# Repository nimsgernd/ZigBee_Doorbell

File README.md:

# ZigBee_Doorbell
I wanted to try to make a nice simple ZigBee doorbell system using some cheap STM32WBA chips and some small Li-Po batteries.

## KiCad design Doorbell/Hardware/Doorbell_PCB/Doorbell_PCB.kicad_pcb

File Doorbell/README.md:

# Doorbell

This folder contains all the files for the doorbell side of the project.

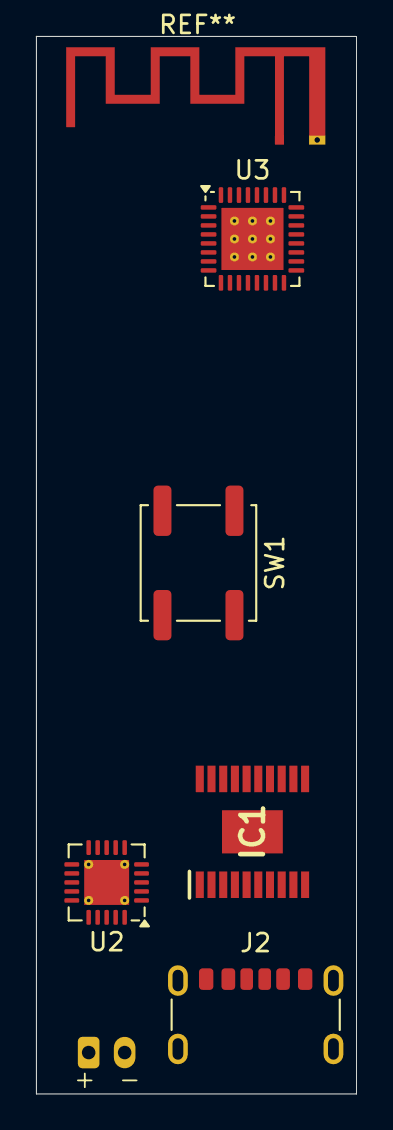
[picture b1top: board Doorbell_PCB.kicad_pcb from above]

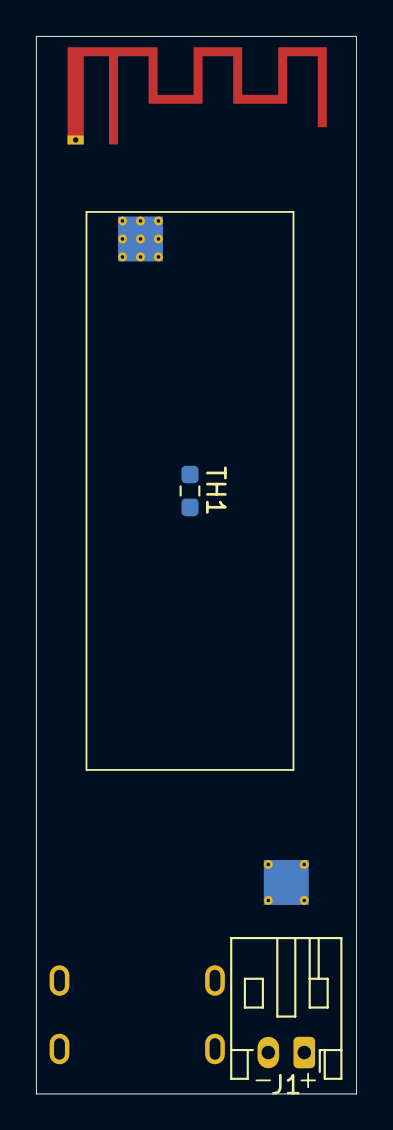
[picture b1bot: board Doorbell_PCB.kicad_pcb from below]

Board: 2 copper layers, 17.8 x 58.8 mm, 7 parts (2 on the bottom side), 5 nets, no tracks yet.

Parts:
IC1: TPS75301QPWP; SOP65P640X120-21N
J1: Conn_01x02_Socket; JST_PH_S2B-PH-K_1x02_P2.00mm_Horizontal
J2: USB_C_Receptacle_PowerOnly_6P; USB_C_Receptacle_GCT_USB4125-xx-x_6P_TopMnt_Horizontal
SW1: SW_Push; SW_Push_1P1T_NO_CK_KSC9xxJ
TH1: Thermistor_NTC; R_0603_1608Metric_Pad0.98x0.95mm_HandSolder
U2: MCP73871-2CC; QFN-20-1EP_4x4mm_P0.5mm_EP2.5x2.5mm_ThermalVias
U3: STM32WBA54KEUx; QFN-32-1EP_5x5mm_P0.5mm_EP3.45x3.45mm_ThermalVias

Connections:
+5V: IC1.3 (IN), IC1.4 (IN), J2.A9 (VBUS), J2.B9 (VBUS), U2.18 (IN), U2.19 (IN)
GND: IC1.1 (GND/HEATSINK), IC1.10 (GND/HEATSINK), IC1.11 (GND/HEATSINK), IC1.17 (GND), IC1.20 (GND/HEATSINK), IC1.21 (HEATSINK), J1.2, J2.A12 (GND), J2.B12 (GND), J2.S1 (SHIELD), U2.10 (V_{SS}), U2.11 (V_{SS}), U2.21 (V_{SS}), U3.33 (VSS)
unnamed: IC1.8 (OUTPUT), IC1.9 (OUTPUT)
unnamed: U2.1 (OUT), U2.20 (OUT)
unnamed: U2.14 (V_{BAT}), U2.15 (V_{BAT})

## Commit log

2025-09-12 Update .gitignore
    Used gitignore.io to generate a .gitignore for C++, Eclipse, VSCode, and KiCAD.
2025-09-12 Added Subdirectories for the Project Parts
2025-09-13 Started Working on PCB
    - Since a large part of the device is the PCB layout size I strted
    general layout along with the schematic design.
